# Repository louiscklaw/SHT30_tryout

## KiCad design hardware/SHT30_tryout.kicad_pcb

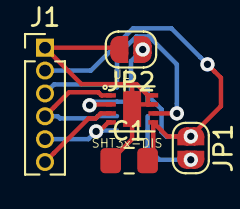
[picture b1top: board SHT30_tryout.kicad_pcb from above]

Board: 2 copper layers, 6 parts (1 on the bottom side), 8 nets.

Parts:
C1: C104,0805; C_0805_2012Metric_Pad1.15x1.40mm_HandSolder
J1: SHT3x_HEADER; PinHeader_1x06_P1.27mm_Vertical
JP1: SCL_SDA; SolderJumper-2_P1.3mm_Open_RoundedPad1.0x1.5mm
JP2: J_ADDR; SolderJumper-2_P1.3mm_Open_RoundedPad1.0x1.5mm
RN1: RN_472,0603; R_Array_Concave_4x0603
U1: SHT3x-DIS

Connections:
+3V3: C1.2, J1.2, JP1.1, RN1.5, RN1.6, U1.5
/ADDR: JP2.1, RN1.3, U1.2
/ALERT: J1.6, U1.3
/NRST: J1.3, RN1.4, U1.6
/SCL: J1.5, RN1.1, U1.4
/SDA: J1.4, RN1.2, U1.1
GND: C1.1, J1.1, JP2.2, U1.7, U1.8, U1.PAD
unnamed: JP1.2, RN1.7, RN1.8

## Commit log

2019-06-07 init commit,
2019-06-07 update datasheet,
2019-06-16 update,
2019-06-21 ignore bak file,
2019-06-21 update for pin assignment,
2020-05-07 ci: init travis build config,
2020-05-07 ci: init travis token,
